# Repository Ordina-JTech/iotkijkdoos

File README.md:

# IoT Kijkdoos

[View inventory Jun-Jul 2017](Inventory.md)

[View inventory Aug-Sep 2017](InventoryAugSep2017.md)

[View order details](Order.md)

[Naming a Bluetooth module](NamingBluetooth.md)

[Connecting to Bluetooth on Android 6+](BluetoothAndroid6plus.md)

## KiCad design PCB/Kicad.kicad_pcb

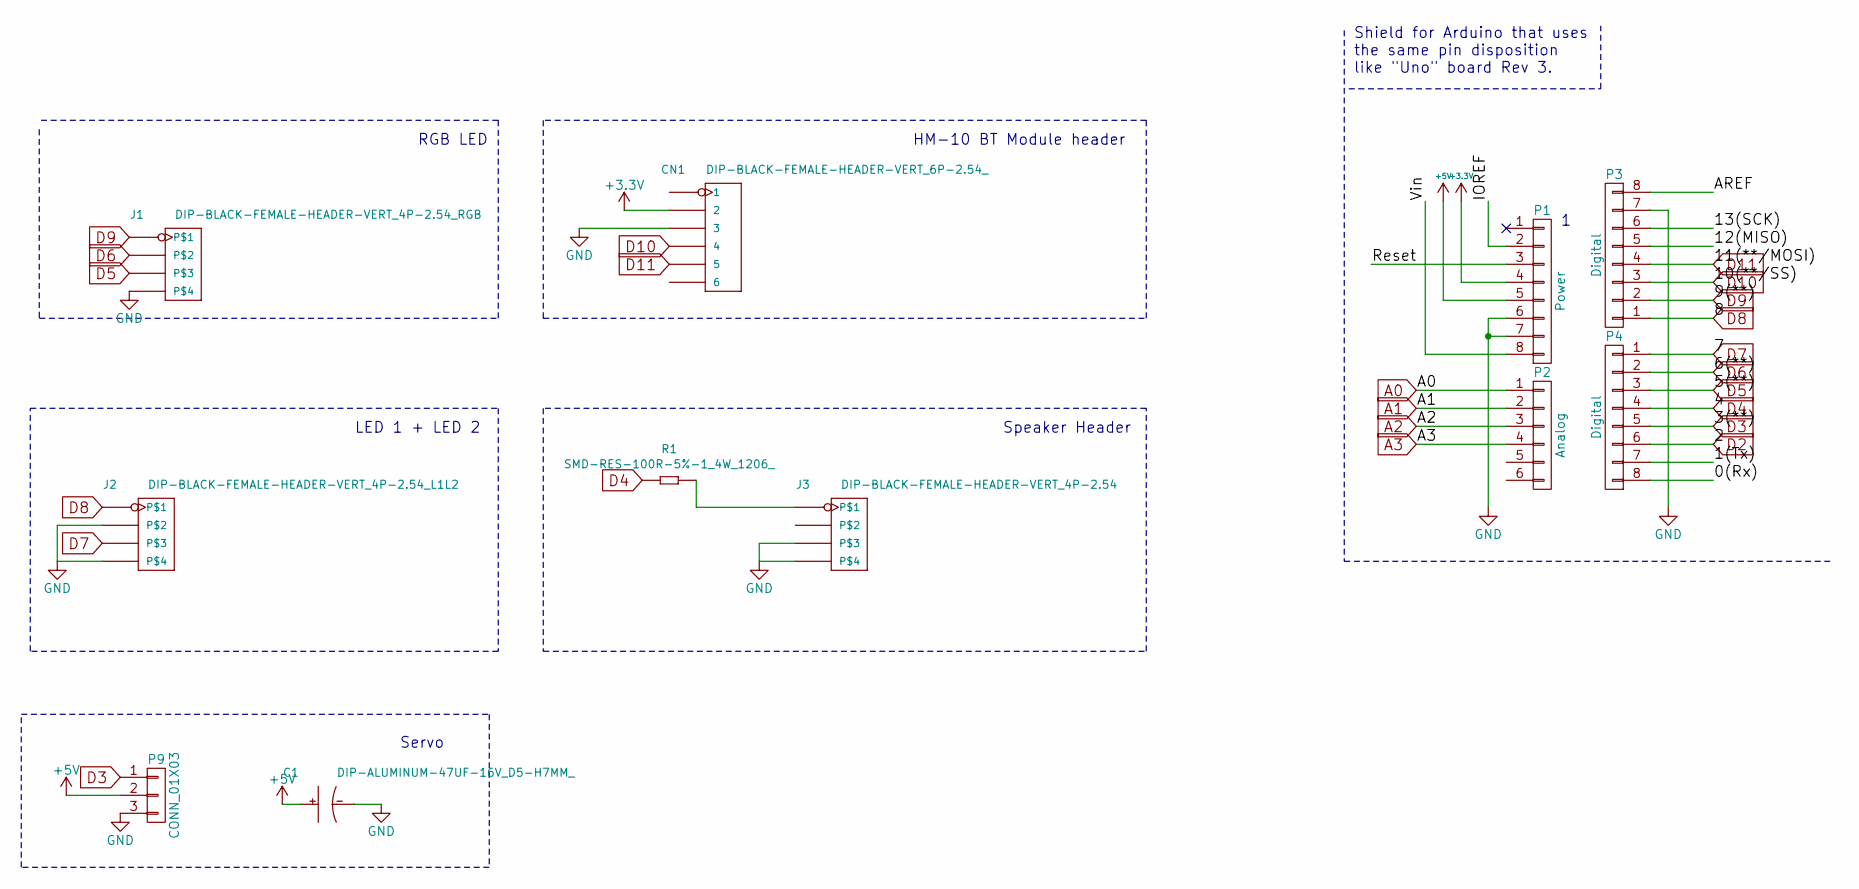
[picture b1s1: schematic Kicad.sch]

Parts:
C1: DIP-ALUMINUM-47UF-16V_D5-H7MM_; CP_Radial_D8.0mm_P5.00mm; MPN KS 100uF_16V
CN1: DIP-BLACK-FEMALE-HEADER-VERT_6P-2.54_; H6-2.54; MPN F185-1106A1BSYC1
J1: DIP-BLACK-FEMALE-HEADER-VERT_4P-2.54_RGB; H4-2.54; MPN F185-1104A1BSYA1
J2: DIP-BLACK-FEMALE-HEADER-VERT_4P-2.54_L1L2; H4-2.54; MPN F185-1104A1BSYA1
J3: DIP-BLACK-FEMALE-HEADER-VERT_4P-2.54; H4-2.54; MPN F185-1104A1BSYA1
P1: Power; H8-2.54
P2: Analog; H6-2.54
P3, P4: Digital; H8-2.54
P9: CONN_01X03; H3-2.54
R1: SMD-RES-100R-5%-1_4W_1206_; R1206; MPN RC1206JR-07100RL

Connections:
+3V3: CN1.2, P1.4
+5V: C1.+, P1.5, P9.2
/0(Rx): P4.8
/1(Tx): P4.7
/12(MISO): P3.5
/13(SCK): P3.6
/AREF: P3.8
/IOREF: P1.2
/Reset: P1.3
/Vin: P1.8
A0: P2.1
A1: P2.2
A2: P2.3
A3: P2.4
D2: P4.6
D3: P4.5, P9.1
D4: P4.4, R1.1
D5: J1.3, P4.3
D6: J1.2, P4.2
D7: J2.3, P4.1
D8: J2.1, P3.1
D9: J1.1, P3.2
D10: CN1.4, P3.3
D11: CN1.5, P3.4
GND: C1.-, CN1.3, J1.4, J2.2, J2.4, J3.3, J3.4, P1.6, P1.7, P3.7, P9.3
unnamed: J3.1, R1.2

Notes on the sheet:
Shield for Arduino that uses the same pin disposition like "Uno" board Rev 3.
RGB LED
LED 1 + LED 2
HM-10 BT Module header
Speaker Header
Servo

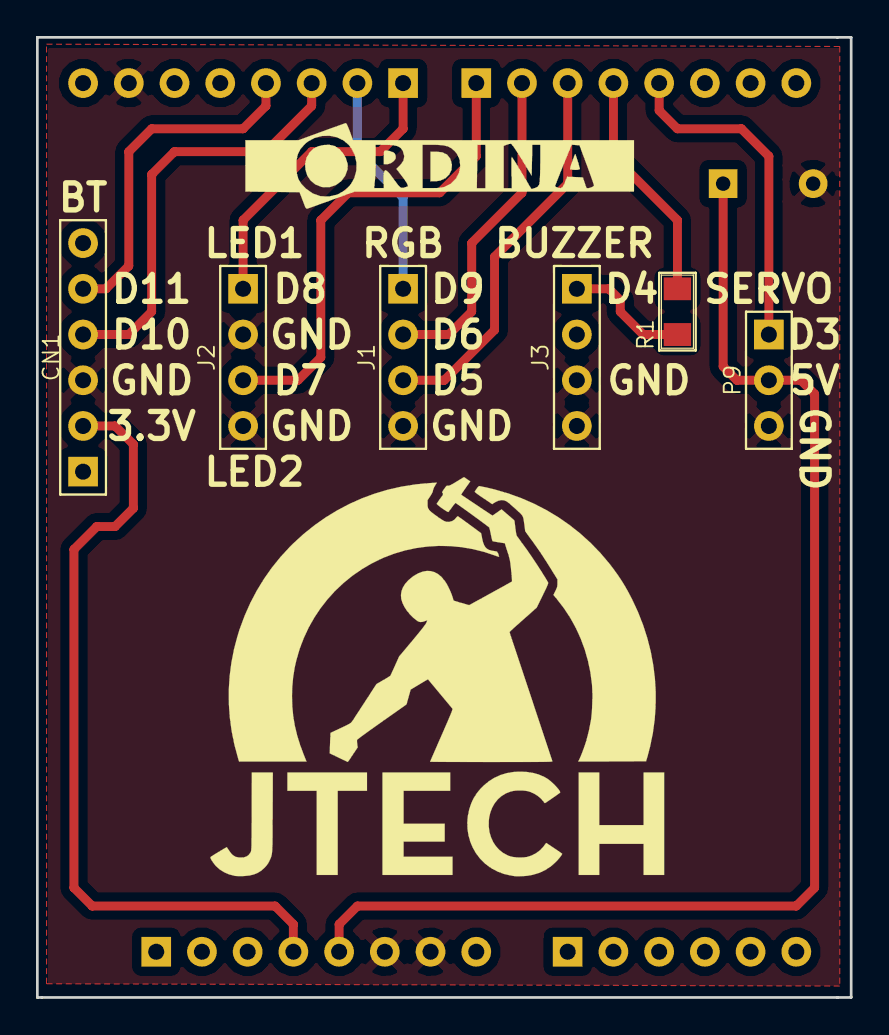
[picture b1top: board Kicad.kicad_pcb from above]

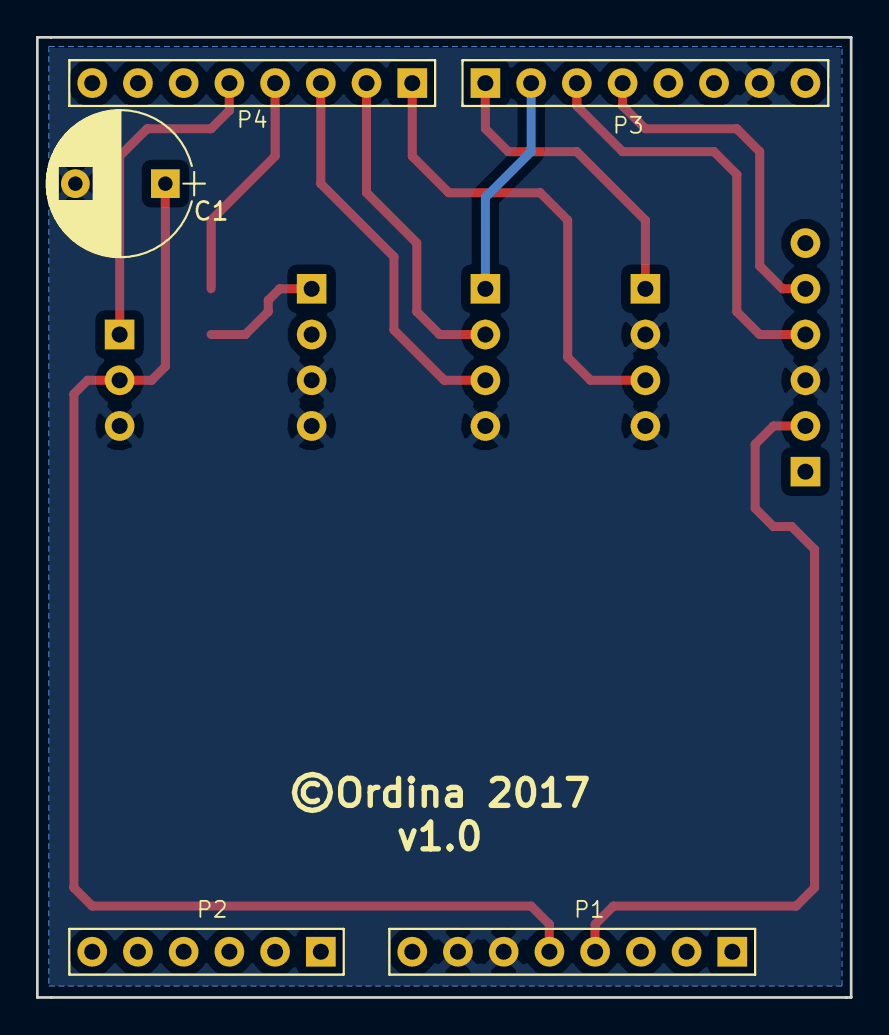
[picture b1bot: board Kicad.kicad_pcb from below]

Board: 2 copper layers, 45.2 x 53.3 mm, 11 parts (5 on the bottom side), 13 nets.

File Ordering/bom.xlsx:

Part/Designator | Manufacture Part Number/Seeed SKU | Quantity
J1, J2, J3 | 320030017 | 3
CN1 | 320030060 | 1
P9 | 320020079 | 1
P1, P3, P4 | 320020080 | 3
P2 | 320020078 | 1
R1 | 301010412 | 1

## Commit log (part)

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2017-02-07 Initial commit of iotkijkdoos.
2017-02-07 .gitignore added for Android App
2017-02-07 Folderstructuur met readme.txt aangemaakt
2017-02-07 check bestand
2017-02-07 Verwijder testbestand
2017-02-07 IOS: initial commit iOS app
2017-02-07 Arduino: initial commit Arduino sketch
2017-02-07 Initial commit bluetooth demo project
2017-02-07 Android: working BLE demo app. TODO: - appbar/toolbar is not shown in ...ScanActivity - appbar is not shown in ...ControlActivity
2017-02-07 Arduino: changed bool powerled1 to isOnLed1. Also for led 2
2017-02-07 Arduino: Added comments
2017-02-07 Visuals: Design van het interieur toegevoegd, gemaakt door Emma.
2017-02-07 IOS: changed the changeColor method and deleted two unused methods.
2017-02-07 IOS: added comments
2017-02-08 IOS: changed the page indicator color, added a label to page 1 for displaying the rgb color and added an enum for reducing the amount of data that has te be sent (rob values) to peripheral.
2017-02-09 Android: backup of IntelliJ projectfiles
2017-02-10 IOS:
2017-02-10 IOS: Removing old project. Starting a new one
2017-02-10 Removed files that are supposed to be in gitignore
2017-02-10 Added navigation to the view box activity
2017-02-13 Added scene transition and the edit activity. Also add project ButterKnife. Because it's awesome... And easy :)
2017-02-13 IOS: refresh control, mainVC, SettingView
2017-02-15 Added GIMP files with the app design for the viewbox
2017-02-15 Added dagger for dependency injection to make the bluetooth service testable
2017-02-16 Added retrolambda. Added code to start scanning for bluetooth devices
2017-02-16 IOS: alle setting views gemaakt, communicatie met Arduino stabieler gemaakt, Arduino: Gezorgd dat na het alarm de lampen die aanstonden weer aangaan.
2017-02-16 Disabled Jack again. Wasn't compiling. Implemented searching for Bluetooth devices. There are no devices in my current surrounding so did not test it with Bluetooth yet. Is tested with Unit tests tho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
2017-02-17 Arduino: Heb de method getRGBvalues() versimpeld. Hierdoor hoeft er vanuit het central device minder characters worden gestuurd. Bij de setServoAngle moet nu het aantal millisecondes ingevoerd worden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
2017-02-17 iOS: refactored RgbVC
2017-02-17 iOS: reset Arduino components als user de app sluit (application will terminate)
2017-02-20 Ignore DS_Store files
2017-02-20 Replaced the default ArrayAdapter with a custom adapter to have more control over the rows. Duplicate devices are ignored.
2017-02-20 Removed some more files from tracking
2017-02-21 iOS: beter commentaar toegevoegd, sliderValueChanged method gerefactored, access modifiers aangepast, Controle over connectedPeripheral alleen in bluetooth class en in mainVC gezorgd dat de user zowe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
2017-02-21 Arduino: Heb wat dingen overzichtelijker en duidelijker gemaakt
2017-02-21 Added the Arduino technical design
2017-02-21 Did some renaming. Implemented the connection to the Arduino Bluetooth module.
2017-02-21 Invoking the ViewBoxActivity now has a reference to the selected device. By a possible Samsung bug, the reference must be wrapped in a Bundle due to class loader issues. See: http://stackoverflow.com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
2017-02-22 Added light weight Java 8 streaming api
2017-02-22 Passed connection over from search activity to control activity. Also that the device is disconnected when the activity is paused. But that's not working yet
2017-02-23 Fixed the unit and android tests
2017-02-23 iOS: comments opgeschoond, namen aangepast voor meer duidelijkheid.
2017-02-27 Created a MockViewBoxRemoteController so it is possible to mock it in the ViewBoxActivity. Added JTech app icons. Implemented a navigation drawer to control the Arduino components. Removed old resour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
2017-02-28 Moved view classes to view package. Added scaled images for the lamp. This fixed a jittered experience when opening and closing the control drawer. Added asking for location permissions. This is nece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
2017-03-01 iOS: enums toegevoegd ipv constant arrays, duidelijkere namen voor methods
2017-03-01 Some renaming and refactoring.
2017-03-01 Added all colors for the disco ball
2017-03-02 iOS: gefixt dat een device niet meer in de table view staat als de peripheral is uitgeschakeld.
2017-03-02 iOS: voorlopige app icon toegevoegd
2017-03-02 iOS: letter+ ‘0’ of ‘1’ zenden aan de hand van de state van de switch button
    Arduino: Led wordt nu aangezet door ‘1’ en ‘0’ te sturen, Led object wordt doorgegeven aan Buzzer, getStatus() en getPinNumber() toegevoegd aan Led class, Led en Rgb classes maken gebruik van readNex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
2017-03-03 Arduino: Duidelijkere naam gebruikt voor method
2017-03-03 iOS: een extra view gemaakt die van alpha waarde verandert als de setting view in en uit slide.
2017-03-07 iOS: nieuw design voor de RGB led, guard statements toegevoegd bij het laden van images, deel van namen aangepast adhv de guidelines van apple
2017-03-07 Added a list of songs to play. Created an adapter that is reusable using functions. Refactored the component enumeration.
2017-03-07 Added the rest of the songs. And fixed a bug caused by changing the color of the light switch of the disco ball.
2017-03-08 iOS: Er zijn wat namen veranderd en afbeeldingen verwijderd
2017-03-08 iOS: Challenge setting view toegevoegd
2017-03-09 iOS: Naamgeving challenges veranderd Arduino: Methodes in main verplaatst naar de juiste class en bluetooth object doorgegeven
2017-03-09 iOS: Als slider 180 graden is, min 1 doen omdat servo van 0-179 gaat.
2017-03-10 iOS: refactoring, constant in enum toegevoegd, starten van refreshen als de app weer actief is (didEnterForeGround). Prepare seque vervangen door viewDidLayoutSubviews
2017-03-13 iOS: 1x, 2x en 3x images toegevoegd. Door de slechte kwaliteit van de tijdelijke images gaat dit niet altijd goed.
2017-03-14 no message
2017-03-15 - Refactored ScanVC. Alles gaat nu via de method checkBluetoothState(), hierdoor hoef ik alleen daar te kijken naar de bluetooth state en isScanning. - hideActiveMessage toegevoegd aan ProgressMessag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
2017-03-15 Hardcoded strings in enum gezet
2017-03-20 Control the television
2017-03-21 iOS: display name en bundle id aangepast
2017-03-21 Distributie files
2017-03-21 Git ignore
2017-03-21 Nu met alle bestanden
2017-03-23 Send a rotation message for every five or eight degrees instead of every degree. This results in a smoother operation of the servo. Also added persistence to the value of the slider. This might be fu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
2017-03-23 Rename of the custom action
2017-03-27 Removed the shared preferences. Rewrote the code to use the fragment life cycle to save the instance state. Because the slider in the TelevisionControlFragment is a custom view, the progress needs to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
2017-03-27 Improved the control of rotating the television
2017-03-28 iOS: Elke nieuwe bluetooth module liet de app crashen omdat de naam ‘null’ was. Dit is opgelost. Arduino: hardcoded ‘1’ en ‘0’ vervangen door variabelen.
2017-03-28 Wat namen veranderd en uitroepteken toegevoegd aan progressMessage
2017-03-28 Handleiding verder uitgewerkt
2017-03-28 Text aangepast
2017-03-28 Wat comments bijgevoegd
2017-03-29 Reviewed the hands-on lab manual and used the word review mode to suggest changes
2017-03-30 De goede versie
2017-03-30 Pin nummer veranderd voor challenge I Broken Light
2017-03-30 Added new activity for when bluetooth is disabled
2017-03-30 Added navigation back to the search activity. Renamed the app.
2017-03-31 Fixed that the user sees two questions of enabling bluetooth after bluetooth was disabled while on the SearchViewBoxActivity. Also isolated the code for adding the BluetoothConnectionFragment to an A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
2017-03-31 New awesome design \o/
2017-03-31 Added logic to handle disconnection while in the ControlViewBoxActivity or when that activity was pushed to the background. The app doesn't disconnect anymore in the onPause
2017-03-31 Reset the view box when connecting and when disconnected by the user
2017-04-03 Initial implementation of pull to refresh for searching for view boxes
2017-04-03 iOS: Interieur veranderd en schaling van afbeeldingen aangepast Arduino: switch statement in SetColor() veranderd door de input in te voeren in de array ‘allColors’
2017-04-03 Afbeeldingen naar 2x gezet ipv 1x
2017-04-03 Added cpp files
2017-04-03 Added refresh item in the overflow menu
2017-04-03 Hamer afbeelding toegevoegd, Disconnect button minder opvallend gemaakt
2017-04-03 ‘Off’ toegevoegd aan array ‘allColors’. Switch loop in setColor() weggehaald. De kleur wordt nu gehaald uit de array ‘allColors’
2017-04-03 Added null checks to the bluetooth adapter to avoid nullpointerexceptions. Added a refresh menu item. Translated text to English.
2017-04-03 Changed another number of translations. Also stop searching for devices when selecting a device
2017-04-03 Speaker image verwijderd
2017-04-03 moved bluetooth to class
2017-04-04 fixed imort vs include moved max angle to servo
2017-04-04 Added the control for the workshop challenges
2017-04-04 Na aanlevering versie 1.0 aan AppStore
2017-04-04 Nog een opa
2017-04-05 Removed the Bluetooth example app. Remove all devices when refresh search. Fix slider color change when first controlling the discoball. Sort search list on device signal strength. Fixed control layo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
2017-04-05 Fixed test for switching off the disco ball. Disabled proguard for the release build. Source is publicly available anyway. Maybe enable it later so the release code is more optimised
2017-04-05 Upped the minSdkVersion to 21 because 18 >= sdk < 21 has bluetooth connection issues.
2017-04-06 Added a frontpage and table of contents.
2017-04-06 Handleiding aangepast
2017-04-11 Lowered the minSdk from 21 to 18. It was set to 21 because the tablet Rik brought had connectivity issues. Several dry run participants received a debug version of the Android app with minSdk 18. The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
2017-04-14 Fixed bug in ScanVC. Ready for update (version 1.1) in Apple Store
2017-04-15 Changed first line in “Sketch Uploaden”.
2017-04-17 Added disclaimer to the manual
2017-04-18 Nieuwe release v1.0.1
2017-04-18 Door de icon die ik hierbij geplaatst heb krijg je een duidelijke icon in git en bijvoorbeeld in SourceTree
2017-04-18 Created an Android Service to have a loosely coupled entity for bluetooth connections.
2017-04-18 Disable the item on the list that was just selected to prevent multiple clicks
2017-04-18 Implemented an Android Service for the Bluetooth session. One bug is that the toast for unexpected disconnection is wrongly displayed.
2017-04-24 Fixed tests where bluetooth is disabled. For some reason the intending statement doesn't work; but the test succeeds without it somehow...
2017-04-24 Listen to the result entered by the user for navigating back to the search activity
2017-04-24 Remove BackgroundService and related Dagger 2 implementation. It added unnecessary complexity.
2017-04-26 Finished the service and the related tests
2017-04-26 Refactoring
    Rename discovery classes so it is obviously about discovering. Rewrite Consumer<Void> to Runnable, because Consumer<Void> does not necessarily make sense.
2017-04-26 Devoxx4Kids manual
    Download RevealJS repository and remove the .git folder. Track changes of this repository. Separate the manuals for the hands-on lab and Devoxx4Kids.
2017-05-01 Add instructions until downloading the app
2017-05-02 Add instructions until the first challenge. I.e. fixing the broken led.
2017-05-03 Add challenge 3 and the functions overview. Move stylesheet from css to scss.
2017-05-04 Add last challenge and the step to create the view box.
2017-05-05 Add missing movies for the rgb led, buzzer and servo.
2017-05-29 Remove the AllSrcCode folder and move its contents in the root
2017-05-29 Add inventory to the readme docs
2017-05-31 Move inventory to separate file and add order details
2017-05-31 Refer to PCB source files
2017-08-25 Adjusted inventory after receiving the orders from this week with adjustments
2017-08-28 Adjusted inventory after naming the 43 HM10 - bt4.0 modules
2017-08-30 Added mario theme
2017-08-30 Changed fatherJacob to starwars theme
2017-08-31 Update README.md
    Removed space to make it working
2017-08-31 How to connect to bluetooth on Android 6+
2017-09-10 Adjusted inventory after given meetup on 6 september. There are 30+ scissors and glue sticks given back after meetings in Endhoven and Utrecht.
2017-10-06 Updated gitignore for kicad

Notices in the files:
PCB/Kicad.kicad_pcb:
©Ordina 2017
